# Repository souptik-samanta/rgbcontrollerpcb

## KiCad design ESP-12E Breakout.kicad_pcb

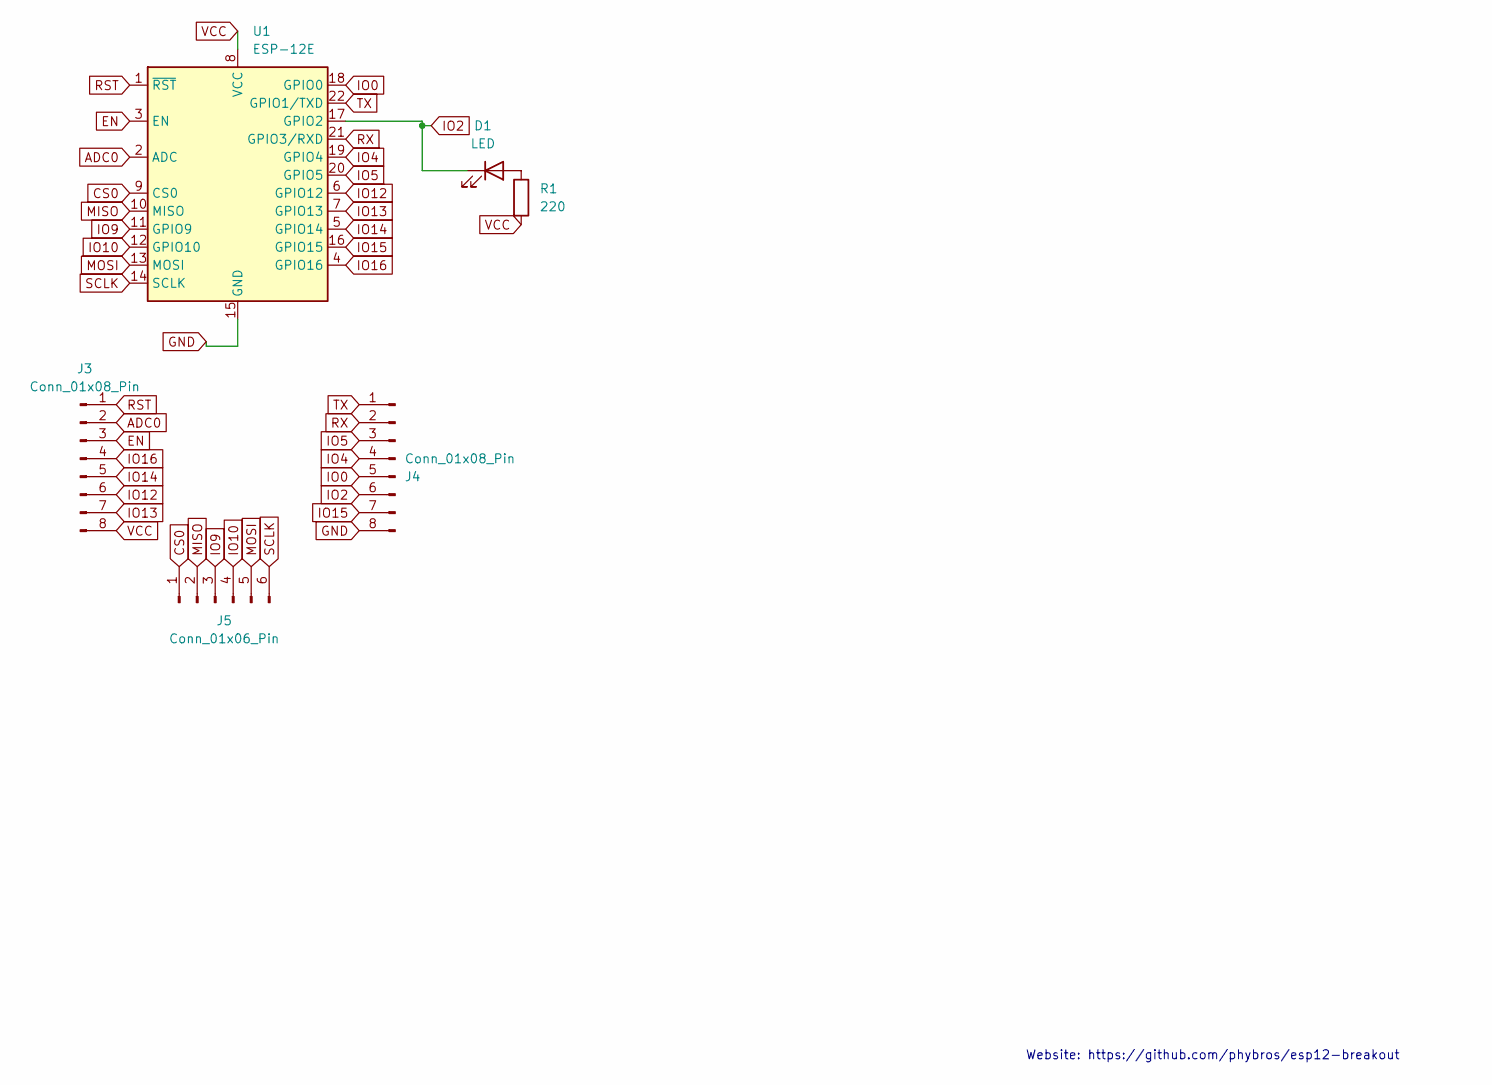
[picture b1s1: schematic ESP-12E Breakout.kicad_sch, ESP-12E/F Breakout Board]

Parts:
D1: LED; LED_0805_2012Metric
J3, J4: Conn_01x08_Pin; PinHeader_1x08_P2.54mm_Vertical
J5: Conn_01x06_Pin; PinHeader_1x06_P2.54mm_Vertical
R1: 220; R_0805_2012Metric_Pad1.20x1.40mm_HandSolder
U1: ESP-12E

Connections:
ADC0: J3.2, U1.2 (ADC)
CS0: J5.1, U1.9 (CS0)
EN: J3.3, U1.3 (EN)
GND: J4.8, U1.15 (GND)
IO0: J4.5, U1.18 (GPIO0)
IO2: D1.1 (K), J4.6, U1.17 (GPIO2)
IO4: J4.4, U1.19 (GPIO4)
IO5: J4.3, U1.20 (GPIO5)
IO9: J5.3, U1.11 (GPIO9)
IO10: J5.4, U1.12 (GPIO10)
IO12: J3.6, U1.6 (GPIO12)
IO13: J3.7, U1.7 (GPIO13)
IO14: J3.5, U1.5 (GPIO14)
IO15: J4.7, U1.16 (GPIO15)
IO16: J3.4, U1.4 (GPIO16)
MISO: J5.2, U1.10 (MISO)
MOSI: J5.5, U1.13 (MOSI)
unnamed: D1.2 (A), R1.1
RST: J3.1, U1.1 (~RST)
RX: J4.2, U1.21 (GPIO3/RXD)
SCLK: J5.6, U1.14 (SCLK)
TX: J4.1, U1.22 (GPIO1/TXD)
VCC: J3.8, R1.2, U1.8 (VCC)

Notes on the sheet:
Website: https://github.com/phybros/esp12-breakout

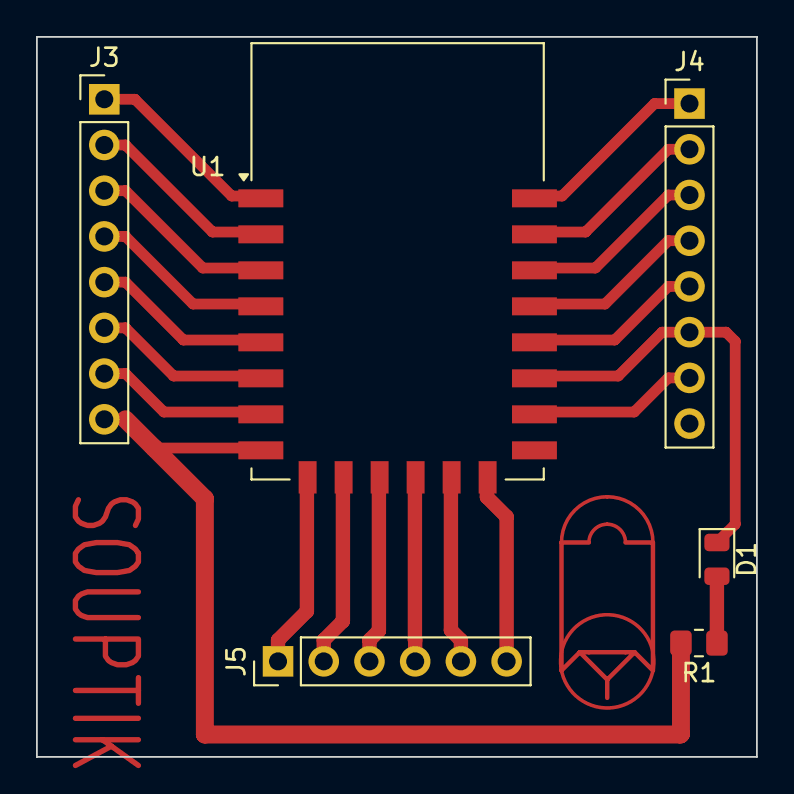
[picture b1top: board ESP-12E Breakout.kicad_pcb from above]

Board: 2 copper layers, 40.0 x 40.0 mm, 6 parts (0 on the bottom side), 23 nets.
